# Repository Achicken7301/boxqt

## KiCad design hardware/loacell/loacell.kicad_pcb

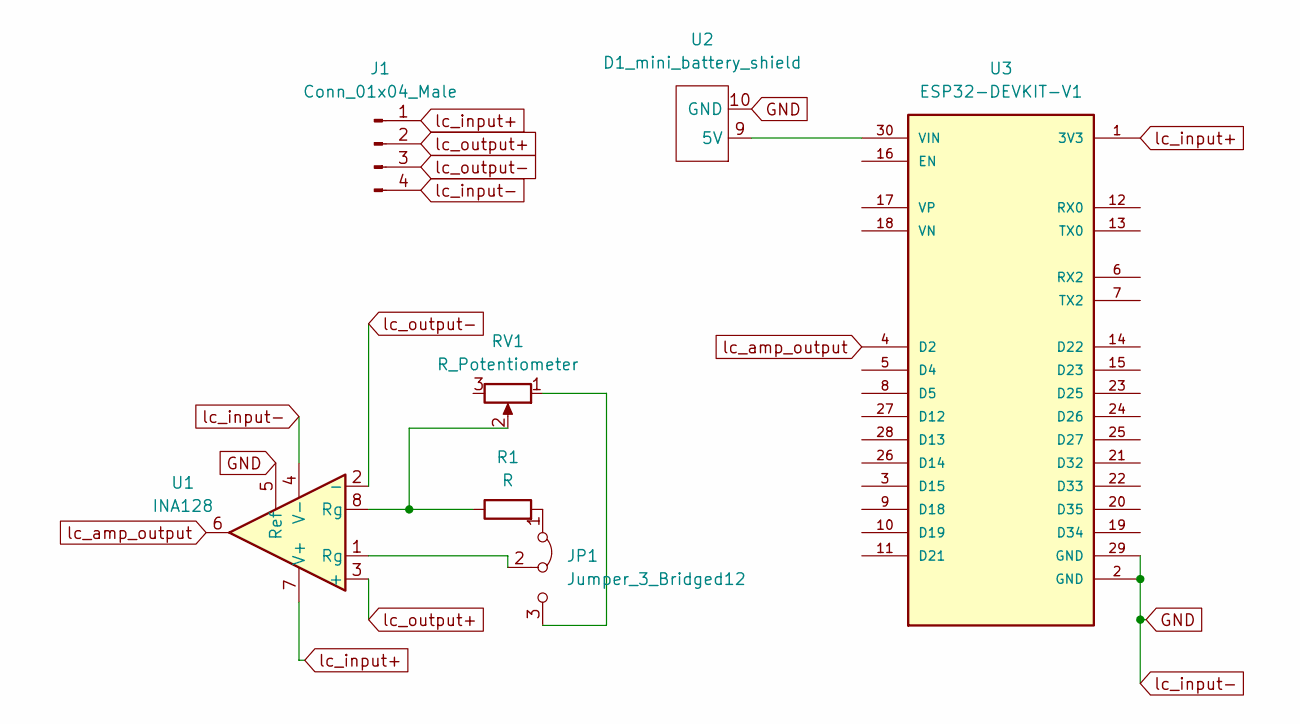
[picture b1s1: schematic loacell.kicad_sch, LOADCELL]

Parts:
J1: Conn_01x04_Male; PinSocket_1x04_P2.54mm_Vertical
JP1: Jumper_3_Bridged12; PinHeader_1x03_P2.54mm_Vertical
R1: R; R_Axial_DIN0207_L6.3mm_D2.5mm_P7.62mm_Horizontal
RV1: R_Potentiometer; Potentiometer_Bourns_3266Y_Vertical
U1: INA128; DIP-8_W7.62mm_LongPads
U2: D1_mini_battery_shield; D1 mini battery shield
U3: ESP32-DEVKIT-V1; MODULE_ESP32_DEVKIT_V1; PARTREV N/A

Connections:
GND: J1.4, U1.4 (V-), U1.5 (Ref), U2.10 (GND), U3.2 (GND), U3.29 (GND)
unnamed: JP1.1 (A), R1.2
unnamed: JP1.3 (B), RV1.1
unnamed: JP1.2 (C), U1.1 (Rg)
unnamed: R1.1, RV1.2, U1.8 (Rg)
unnamed: U2.9 (5V), U3.30 (VIN)
lc_amp_output: U1.6, U3.4 (D2)
lc_input+: J1.1, U1.7 (V+), U3.1 (3V3)
lc_output+: J1.2, U1.3 (+)
lc_output-: J1.3, U1.2 (-)

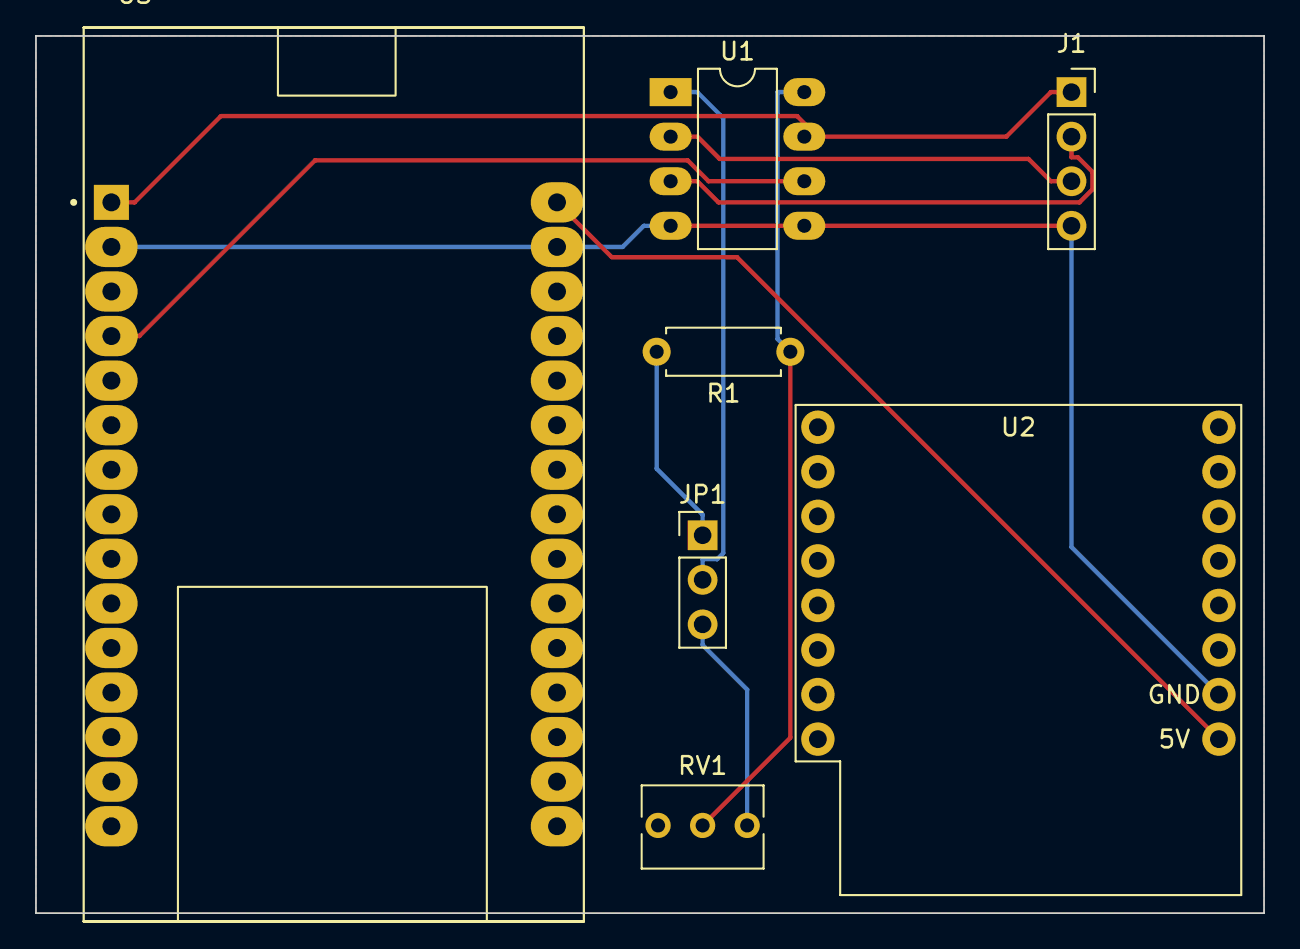
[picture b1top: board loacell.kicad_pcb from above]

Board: 2 copper layers, 70.0 x 50.0 mm, 7 parts (0 on the bottom side), 10 nets.

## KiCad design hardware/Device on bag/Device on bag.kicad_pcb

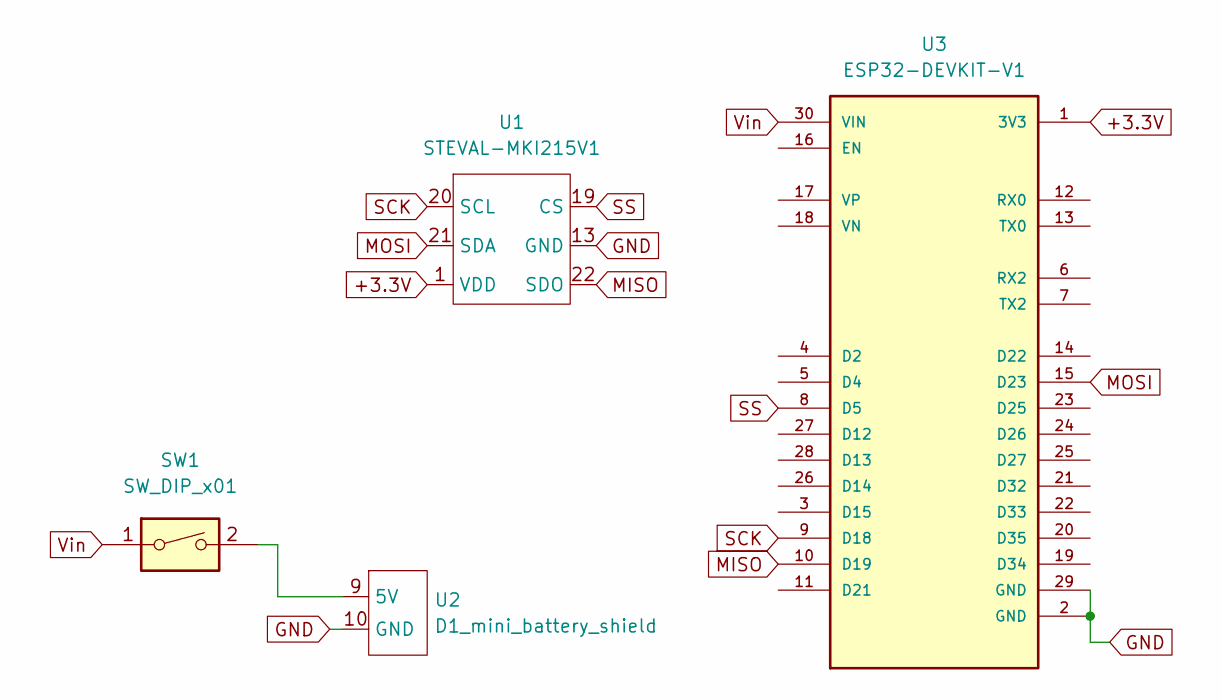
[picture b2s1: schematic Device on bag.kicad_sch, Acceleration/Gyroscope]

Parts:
SW1: SW_DIP_x01; SW_Push_2P2T_Toggle_CK_PVA2xxH1xxxxxxV2
U1: STEVAL-MKI215V1
U2: D1_mini_battery_shield; D1 mini battery shield
U3: ESP32-DEVKIT-V1; MODULE_ESP32_DEVKIT_V1; PARTREV N/A

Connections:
+3.3V: U1.1 (VDD), U3.1 (3V3)
GND: U1.13 (GND), U2.10 (GND), U3.2 (GND), U3.29 (GND)
MISO: U1.22 (SDO), U3.10 (D19)
MOSI: U1.21 (SDA), U3.15 (D23)
unnamed: SW1.2, U2.9 (5V)
SCK: U1.20 (SCL), U3.9 (D18)
SS: U1.19 (CS), U3.8 (D5)
Vin: SW1.1, U3.30 (VIN)

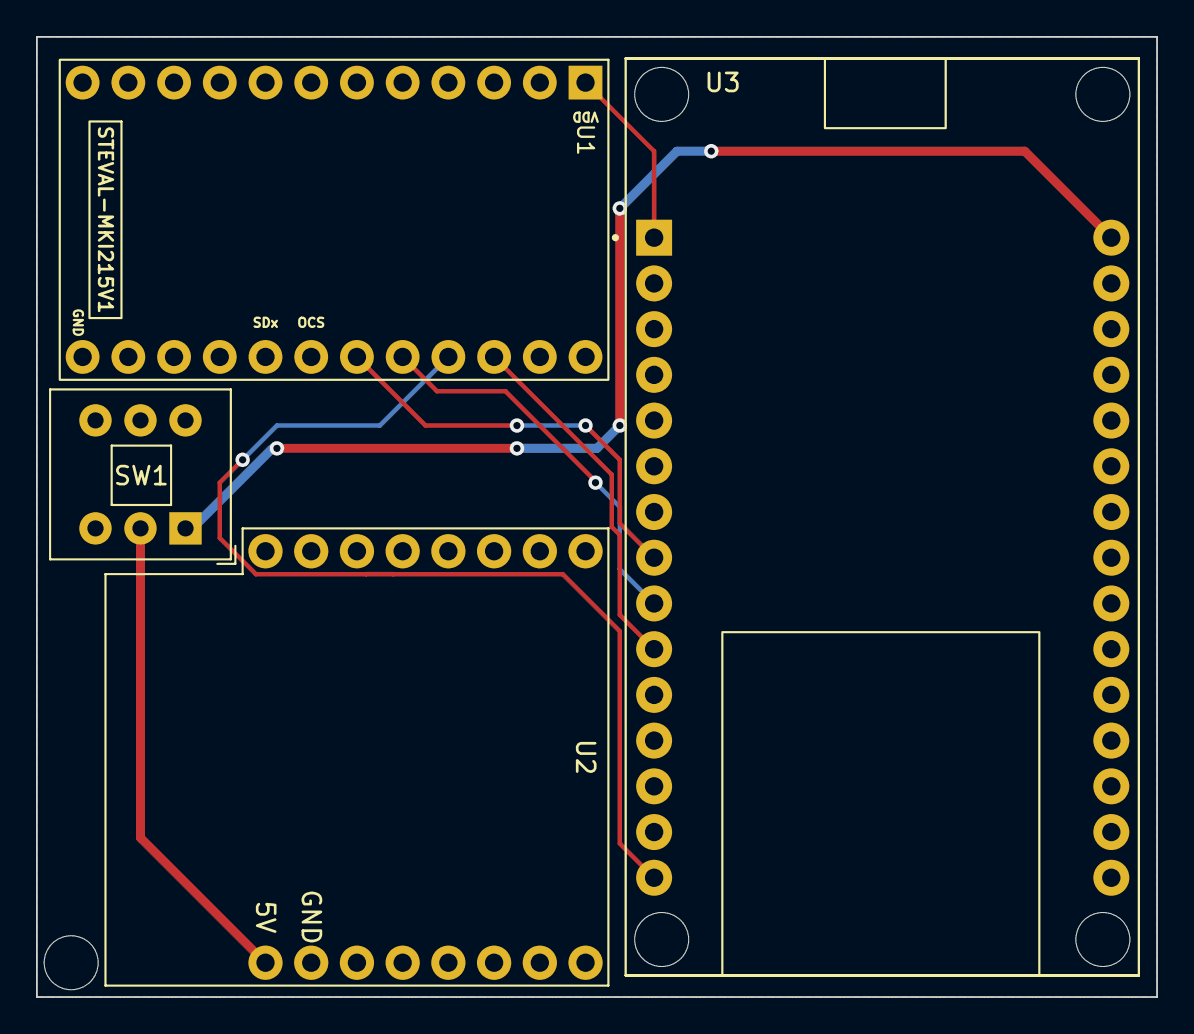
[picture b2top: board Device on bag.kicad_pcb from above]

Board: 2 copper layers, 62.2 x 53.3 mm, 4 parts (0 on the bottom side), 8 nets.

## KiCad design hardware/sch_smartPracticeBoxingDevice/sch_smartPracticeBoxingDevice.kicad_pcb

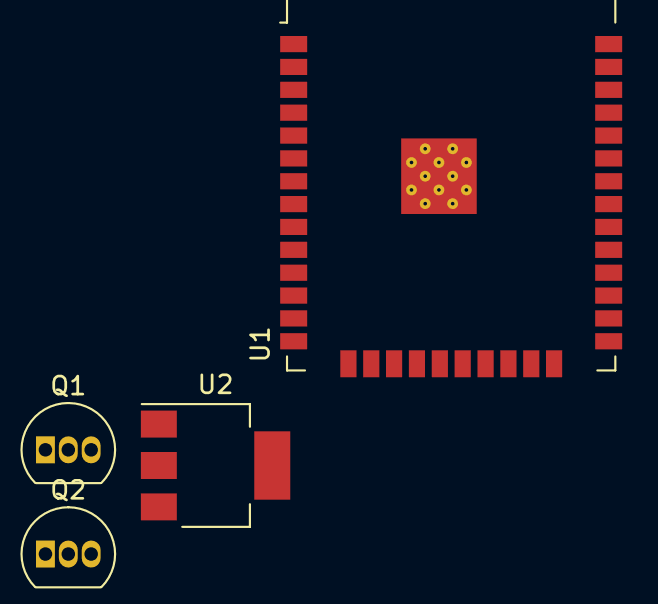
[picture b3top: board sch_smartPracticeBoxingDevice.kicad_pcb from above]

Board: 2 copper layers, 4 parts (0 on the bottom side), 4 nets, no tracks yet.

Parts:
Q1, Q2: S8050; TO-92_Inline
U1: ESP32-WROOM-32
U2: NCP1117-1.5_SOT223; SOT-223-3_TabPin2

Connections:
/3V3: U1.2 (VDD), U2.2 (VO)
/EN: Q2.3 (C), U1.3 (EN)
/IO0: Q1.3 (C), U1.25 (IO0)
GND: U1.1 (GND), U1.15 (GND), U1.38 (GND), U1.39 (GND), U2.1 (GND)

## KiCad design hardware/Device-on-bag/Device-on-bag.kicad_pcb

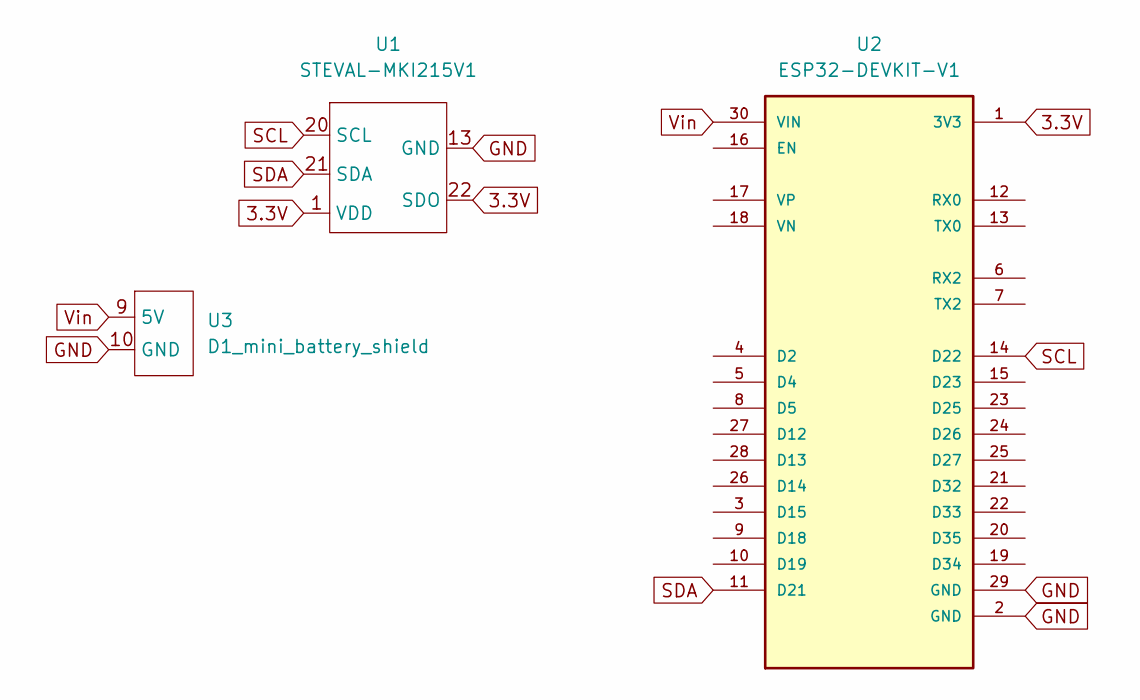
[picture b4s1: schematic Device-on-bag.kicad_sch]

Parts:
U1: STEVAL-MKI215V1
U2: ESP32-DEVKIT-V1; MODULE_ESP32_DEVKIT_V1; PARTREV N/A
U3: D1_mini_battery_shield; D1 mini battery shield

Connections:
3.3V: U1.1 (VDD), U1.22 (SDO), U2.1 (3V3)
GND: U1.13 (GND), U2.2 (GND), U2.29 (GND), U3.10 (GND)
SCL: U1.20 (SCL), U2.14 (D22)
SDA: U1.21 (SDA), U2.11 (D21)
Vin: U2.30 (VIN), U3.9 (5V)

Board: 2 copper layers, 3 parts (0 on the bottom side), 5 nets, no tracks yet.

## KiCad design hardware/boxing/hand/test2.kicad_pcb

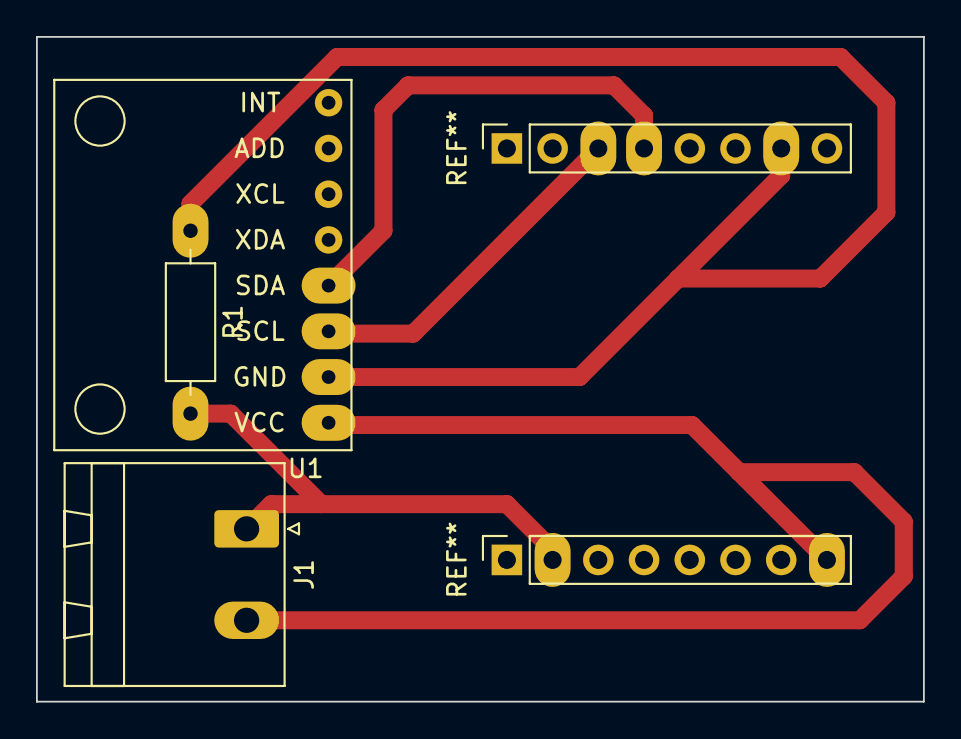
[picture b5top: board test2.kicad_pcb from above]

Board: 2 copper layers, 49.3 x 36.9 mm, 3 parts (0 on the bottom side), 3 nets.

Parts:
J1: Screw_Terminal_01x02; PhoenixContact_MSTBA_2,5_2-G-5,08_1x02_P5.08mm_Horizontal
R1: R; R_Axial_DIN0207_L6.3mm_D2.5mm_P10.16mm_Horizontal
U1: module_mpu6050

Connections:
3v3: J1.2, U1.1 (VCC)
unnamed: J1.1, R1.2
gnd: R1.1, U1.2 (GND)

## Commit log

2022-05-15 feature: send via bluetooth
2022-05-15 Style: show title in plot
2022-05-30 fix gyroscope range
    from 250 degree to 2000 degree
2022-05-30 style update main display
2022-05-30 feat realtime + optimize
    - update realtime
    - optimize code
2022-05-30 test
2022-05-31 too lazy to write meaningfull commit
2022-06-30 small update
2022-07-10 Add feature
    Scan for COM port
2022-08-16 Feature (packages required)
    How to generate packages requirements.txt: https://mothergeo-py.readthedocs.io/en/latest/development/how-to/venv-win.html#add-libraries-and-create-a-requirements-txt-file
    pip freeze > requirements.txt
    pip install -r requirements.txt
2022-08-18 Feat(main.py)
    Record 2 COM at once.
    Export .csv to each COM
2022-08-18 Refactor(Testing folder)
    Move to root dir
2022-08-19 Feat(main.py) port scan faster
    https://stackoverflow.com/questions/55816358/how-to-obtain-bluetooth-port-direction-with-pyserial
2022-08-22 Fix(main.py) self.port_on_hand
    self.port_on_hand = self.portOnBag.currentText() not portOnHAND.currentText()
2022-09-08 refactor & testing
2022-09-08 Software feat force + accel
2022-09-08 hardware update Device on hand
2022-09-09 hardware update
2022-09-09 Fix change name
2022-09-17 update hardware
2022-09-17 update gitignore
2022-09-17 Update CNN
2022-09-29 raw data
2022-09-29 fix header
2022-09-29 fix increase more sample rate
2022-09-29 check sample rate of a COM port
2022-10-04 feat record one device Only
2022-10-04 Refactor code and change ui for oneDeviceRecord
2022-10-04 fix remove Lis331 code
2022-10-04 fix there no clearListBtn
2022-10-06 feat(main.py) reduce CPU
    by adding timer.stop()
2022-10-06 feat(main.py) reduce CPU load
    timer.stop()
2022-10-09 update ui
2022-10-10 refactor data folder
2022-10-10 feat more data preprocess
2022-11-01 update device on bag hardware
2023-01-20 View Add Error Message
2023-01-20 Fix Load from CSV & View
2023-02-14 fix(window_mask)
    remove everything in window_mask before start a new session
2023-02-14 refactor(use database)
2023-02-15 view(update to graph)
2023-02-27 feat(user app) real time plot data
2023-04-22 stable
2023-04-25 update something i dont know
2023-05-21 final commit i hope
2023-05-27 final Thesis
2023-07-22 init
